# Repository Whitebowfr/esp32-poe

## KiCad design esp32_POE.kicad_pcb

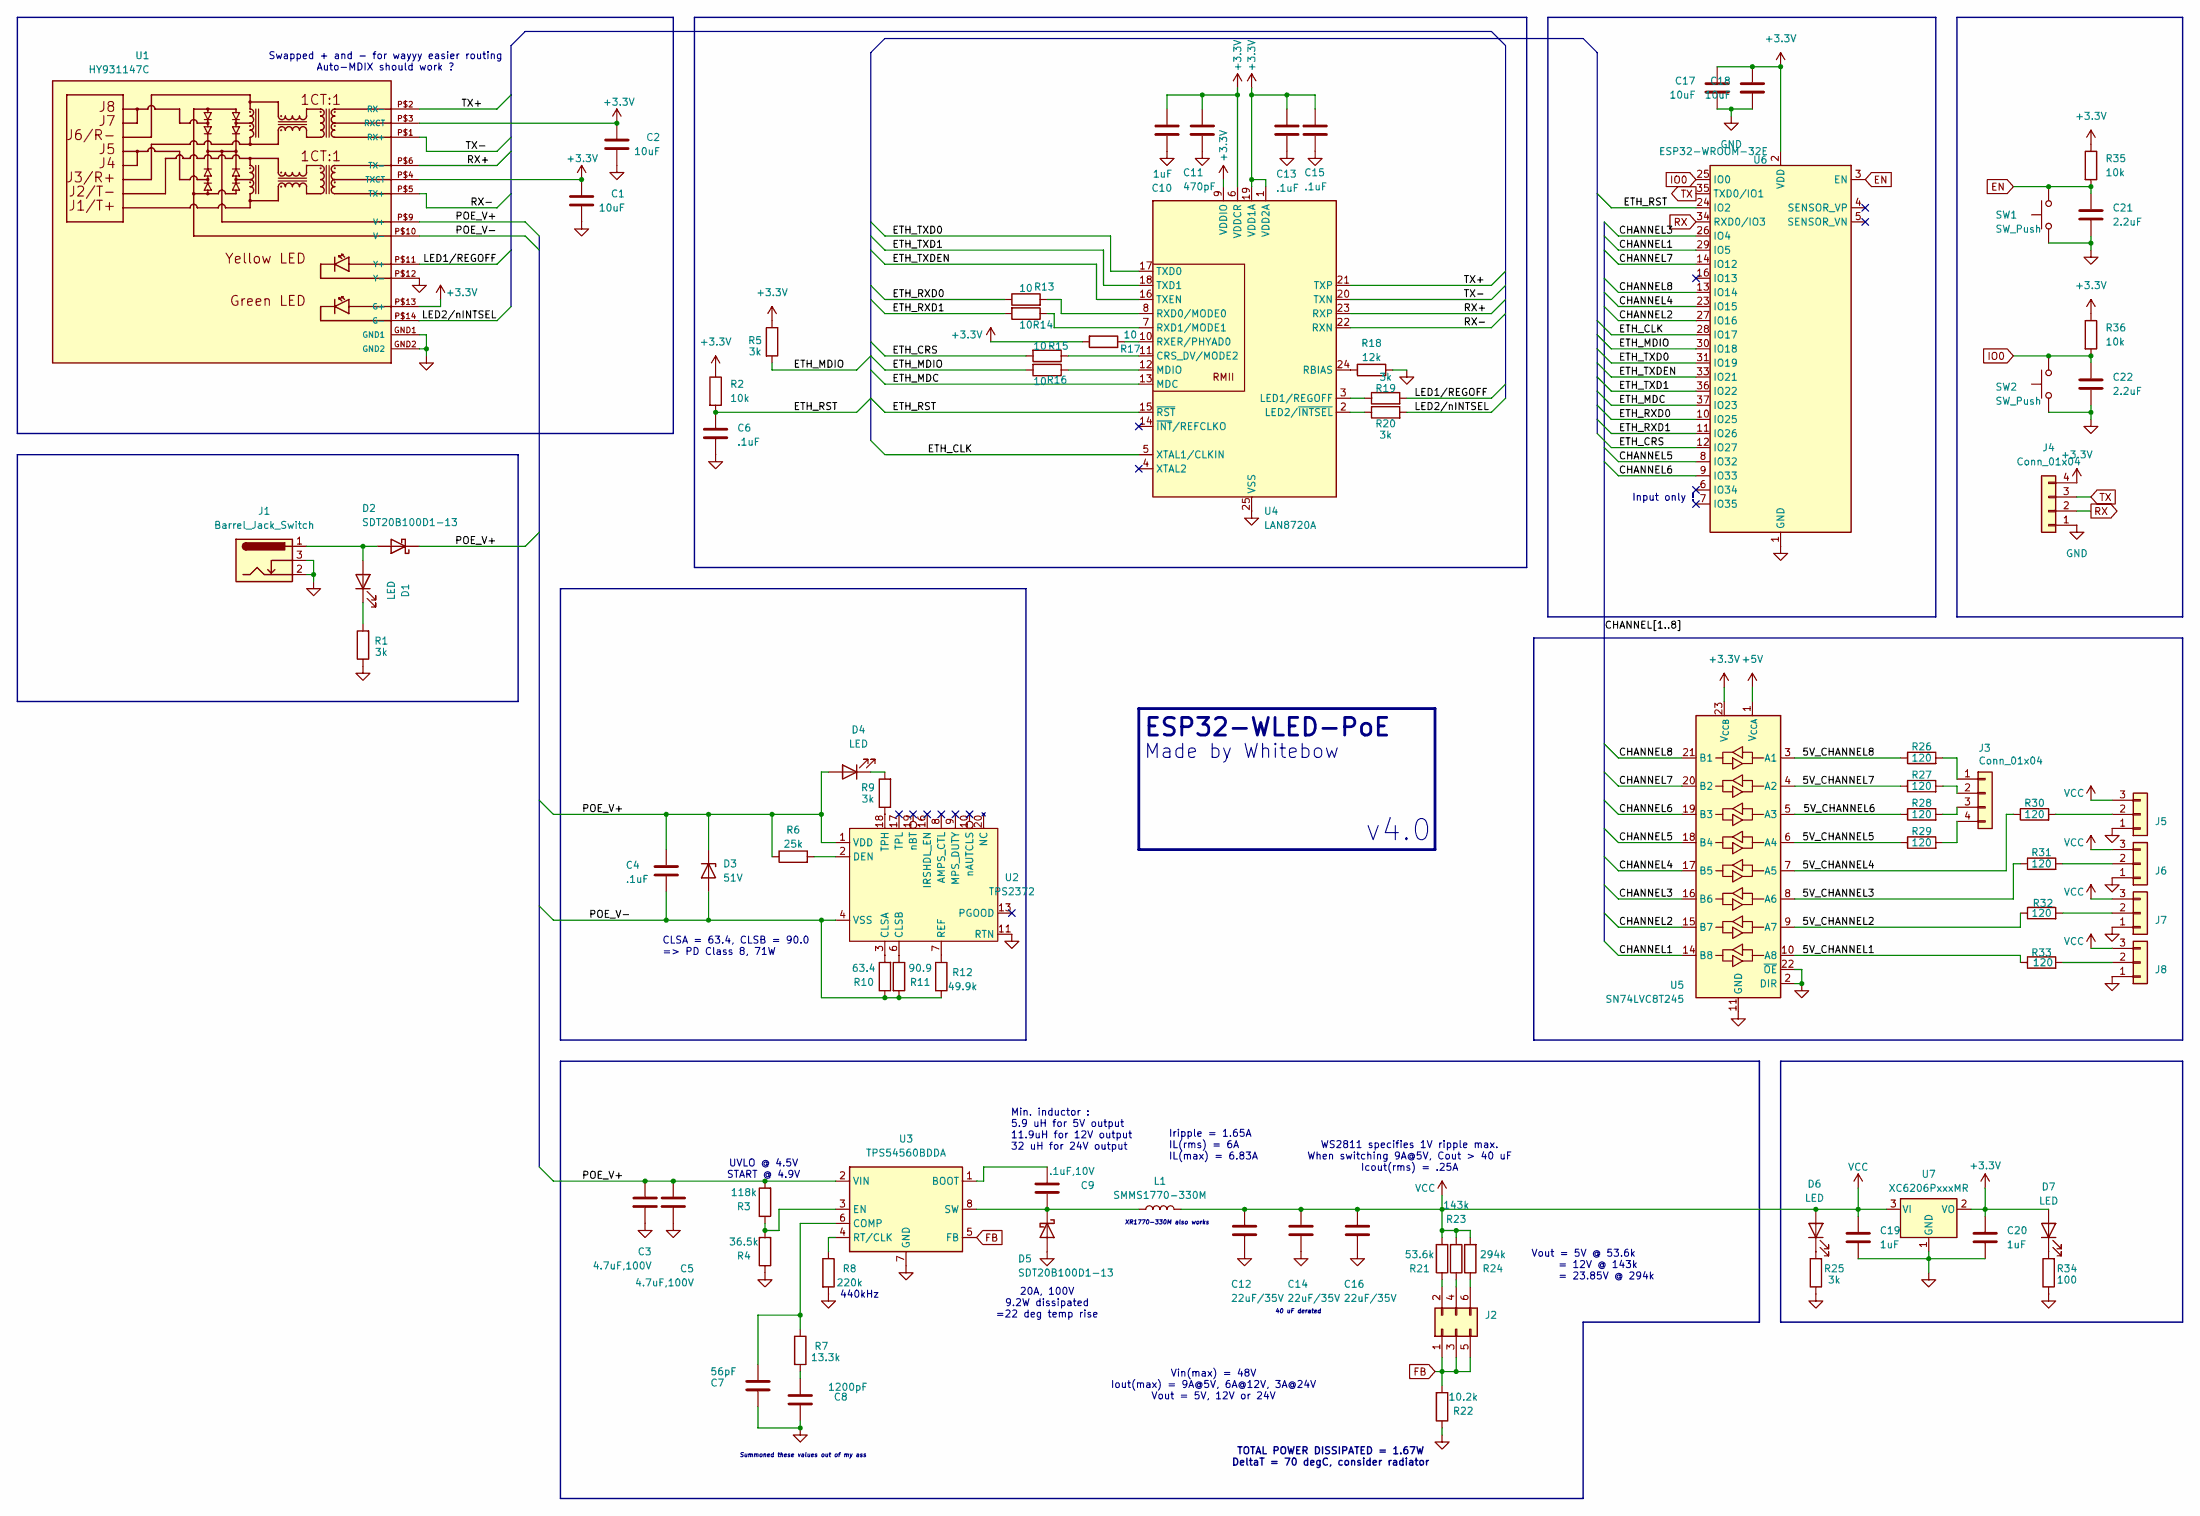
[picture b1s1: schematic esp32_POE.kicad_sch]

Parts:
C1, C2, C17, C18: 10uF; C_0603_1608Metric
C3, C5: 4.7uF,100V; C_1206_3216Metric
C4, C6, C13, C15: .1uF; C_0603_1608Metric
C7: 56pF; C_0603_1608Metric
C8: 1200pF; C_0603_1608Metric
C9: .1uF,10V; C_0603_1608Metric
C10, C19, C20: 1uF; C_0603_1608Metric
C11: 470pF; C_0603_1608Metric
C12, C14, C16: 22uF/35V; C_0805_2012Metric
C21, C22: 2.2uF; C_0603_1608Metric
D1, D4, D6, D7: LED; LED_0603_1608Metric
D2, D5: SDT20B100D1-13; TO-252-2
D3: 51V; D_SMA
J1: Barrel_Jack_Switch; BarrelJack_Horizontal; LCSC C22459638
J2: Conn_02x03_Odd_Even; PinHeader_2x03_P2.54mm_Vertical
J3: Conn_01x04; PinSocket_1x04_P2.54mm_Vertical
J4: Conn_01x04; PinSocket_1x04_P1.27mm_Vertical
J5, J6, J7, J8: Conn_01x03; JST_XH_B3B-XH-AM_1x03_P2.50mm_Vertical
L1: SMMS1770-330M; L_Vishay_IHLP-6767
R1, R5, R9, R19, R20, R25: 3k; R_0603_1608Metric
R2, R35, R36: 10k; R_0603_1608Metric
R3: 118k; R_0603_1608Metric
R4: 36.5k; R_0603_1608Metric
R6: 25k; R_0603_1608Metric
R7: 13.3k; R_0603_1608Metric
R8: 220k; R_0603_1608Metric
R10: 63.4; R_0603_1608Metric
R11: 90.9; R_0603_1608Metric
R12: 49.9k; R_0603_1608Metric
R13, R14, R15, R16, R17: 10; R_0603_1608Metric
R18: 12k; R_0603_1608Metric
R21: 53.6k; R_0603_1608Metric
R22: 10.2k; R_0603_1608Metric
R23: 143k; R_0603_1608Metric
R24: 294k; R_0603_1608Metric
R26, R27, R28, R29, R30, R31, R32, R33: 120; R_0603_1608Metric
R34: 100; R_0603_1608Metric
SW1, SW2: SW_Push; SW_Push_SPST_NO_Alps_SKRK; LCSC C720477
U1: HY931147C
U2: TPS2372; Texas_RGW0020A_VQFN-20-1EP_5x5mm_P0.65mm_EP3.15x3.15mm
U3: TPS54560BDDA; Texas_R-PDSO-G8_EP2.95x4.9mm_Mask2.4x3.1mm_ThermalVias
U4: LAN8720A; VQFN-24-1EP_4x4mm_P0.5mm_EP2.5x2.5mm_ThermalVias
U5: SN74LVC8T245; TSSOP-24_4.4x7.8mm_P0.65mm
U6: ESP32-WROOM-32E
U7: XC6206PxxxMR; SOT-23-3

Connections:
+3.3V: C1.2, C2.2, C10.2, C11.1, C13.1, C15.1, C17.1, C18.1, C20.1, D7.2 (A), J4.4, R2.1, R5.1, R17.2, R35.1, R36.1, U1.P$3 (RXCT), U1.P$4 (TXCT), U1.P$13 (G+), U4.1 (VDD2A), U4.6 (VDDCR), U4.9 (VDDIO), U4.19 (VDD1A), U5.23 (V_{CCB}), U5.24 (V_{CCB}), U6.2 (VDD), U7.2 (VO)
+5V: U5.1 (V_{CCA})
/5V_CHANNEL1: R33.1, U5.10 (A8)
/5V_CHANNEL2: R32.1, U5.9 (A7)
/5V_CHANNEL3: R31.1, U5.8 (A6)
/5V_CHANNEL4: R30.1, U5.7 (A5)
/5V_CHANNEL5: R29.1, U5.6 (A4)
/5V_CHANNEL6: R28.1, U5.5 (A3)
/5V_CHANNEL7: R27.1, U5.4 (A2)
/5V_CHANNEL8: R26.1, U5.3 (A1)
/CHANNEL1: U5.14 (B8), U6.29 (IO5)
/CHANNEL2: U5.15 (B7), U6.27 (IO16)
/CHANNEL3: U5.16 (B6), U6.26 (IO4)
/CHANNEL4: U5.17 (B5), U6.23 (IO15)
/CHANNEL5: U5.18 (B4), U6.8 (IO32)
/CHANNEL6: U5.19 (B3), U6.9 (IO33)
/CHANNEL7: U5.20 (B2), U6.14 (IO12)
/CHANNEL8: U5.21 (B1), U6.13 (IO14)
/ETH_CLK: U4.5 (XTAL1/CLKIN), U6.28 (IO17)
/ETH_CRS: R15.2, U6.12 (IO27)
/ETH_MDC: U4.13 (MDC), U6.37 (IO23)
/ETH_MDIO: R5.2, R16.2, U6.30 (IO18)
/ETH_RST: C6.1, R2.2, U4.15 (~RST), U6.24 (IO2)
/ETH_RXD0: R13.1, U6.10 (IO25)
/ETH_RXD1: R14.2, U6.11 (IO26)
/ETH_TXD0: U4.17 (TXD0), U6.31 (IO19)
/ETH_TXD1: U4.18 (TXD1), U6.36 (IO22)
/ETH_TXDEN: U4.16 (TXEN), U6.33 (IO21)
/LED1/REGOFF: R19.2, U1.P$11 (Y+)
/LED2/nINTSEL: R20.2, U1.P$14 (G-)
/POE_V+: C3.1, C4.1, C5.1, D2.2 (K), D3.1 (K), D4.2 (A), R3.2, R6.1, U1.P$9 (V+), U2.1 (VDD), U3.2 (VIN)
/POE_V-: C4.2, D3.2 (A), R10.1, R11.2, R12.2, U1.P$10 (V-), U2.4 (VSS), U2.5 (VSS), U2.21 (EPAD)
/RX+: U1.P$6 (TX-), U4.23 (RXP)
/RX-: U1.P$5 (TX+), U4.22 (RXN)
/TX+: U1.P$2 (RX-), U4.21 (TXP)
/TX-: U1.P$1 (RX+), U4.20 (TXN)
EN: C21.1, R35.2, SW1.2, U6.3 (EN)
FB: J2.1, J2.3, J2.5, R22.2, U3.5 (FB)
GND: C1.1, C2.1, C3.2, C5.2, C6.2, C7.1, C8.1, C10.1, C11.2, C12.2, C13.2, C14.2, C15.2, C16.2, C17.2, C18.2, C19.2, C20.2, C21.2, C22.2, D5.1 (A), D5.3 (A), J1.2, J1.3, J4.1, J5.1, J6.1, J7.1, J8.1, R1.1, R4.1, R8.2, R18.1, R22.1, R25.1, R34.1, SW1.1, SW2.1, U1.GND1, U1.GND2, U1.P$12 (Y-), U2.11 (RTN), U2.12 (RTN), U3.7 (GND), U3.9 (GND), U4.25 (VSS), U5.2 (DIR), U5.11 (GND), U5.12 (GND), U5.13 (GND), U5.22 (~OE), U6.1 (GND), U6.15 (GND), U6.38 (GND), U6.39 (GND), U7.1 (GND)
IO0: C22.1, R36.2, SW2.2, U6.25 (IO0)
unnamed: C8.2, R7.2
unnamed: D1.2 (A), D2.1 (A), D2.3 (A), J1.1
unnamed: D1.1 (K), R1.2
unnamed: D4.1 (K), R9.2
unnamed: C9.1, D5.2 (K), L1.1, U3.8 (SW)
unnamed: D6.1 (K), R25.2
unnamed: D7.1 (K), R34.2
unnamed: J2.2, R21.1
unnamed: J2.4, R23.1
unnamed: J2.6, R24.1
unnamed: J3.1, R26.2
unnamed: J3.2, R27.2
unnamed: J3.3, R28.2
unnamed: J3.4, R29.2
unnamed: J5.2, R30.2
unnamed: J6.2, R31.2
unnamed: J7.2, R32.2
unnamed: J8.2, R33.2
unnamed: R10.2, U2.3 (CLSA)
unnamed: R11.1, U2.6 (CLSB)
unnamed: R6.2, U2.2 (DEN)
unnamed: R12.1, U2.7 (REF)
unnamed: R9.1, U2.18 (TPH)
unnamed: C9.2, U3.1 (BOOT)
unnamed: C7.2, R7.1, U3.6 (COMP)
unnamed: R3.1, R4.2, U3.3 (EN)
unnamed: R8.1, U3.4 (RT/CLK)
unnamed: R15.1, U4.11 (CRS_DV/MODE2)
unnamed: R19.1, U4.3 (LED1/REGOFF)
unnamed: R20.1, U4.2 (LED2/~INTSEL)
unnamed: R16.1, U4.12 (MDIO)
unnamed: R18.2, U4.24 (RBIAS)
unnamed: R13.2, U4.8 (RXD0/MODE0)
unnamed: R14.1, U4.7 (RXD1/MODE1)
unnamed: R17.1, U4.10 (RXER/PHYAD0)
RX: J4.2, U6.34 (RXD0/IO3)
TX: J4.3, U6.35 (TXD0/IO1)
VCC: C12.1, C14.1, C16.1, C19.1, D6.2 (A), J5.3, J6.3, J7.3, J8.3, L1.2, R21.2, R23.2, R24.2, U7.3 (VI)

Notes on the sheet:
ESP32-WLED-PoE
Vout = 5V @ 53.6k = 12V @ 143k = 23.85V @ 294k
CLSA = 63.4, CLSB = 90.0 => PD Class 8, 71W
TOTAL POWER DISSIPATED = 1.67W DeltaT = 70 degC, consider radiator
Iripple = 1.65A IL(rms) = 6A IL(max) = 6.83A
XR1770-330M also works
Input only !
440kHz
Made by Whitebow
Swapped + and - for wayyy easier routing Auto-MDIX should work ?
40 uF derated
Vin(max) = 48V Iout(max) = 9A@5V, 6A@12V, 3A@24V Vout = 5V, 12V or 24V
UVLO @ 4.5V START @ 4.9V
Min. inductor : 5.9 uH for 5V output 11.9uH for 12V output 32 uH for 24V output
Summoned these values out of my ass
WS2811 specifies 1V ripple max. When switching 9A@5V, Cout > 40 uF Icout(rms) = .25A
20A, 100V 9.2W dissipated =22 deg temp rise
v4.0

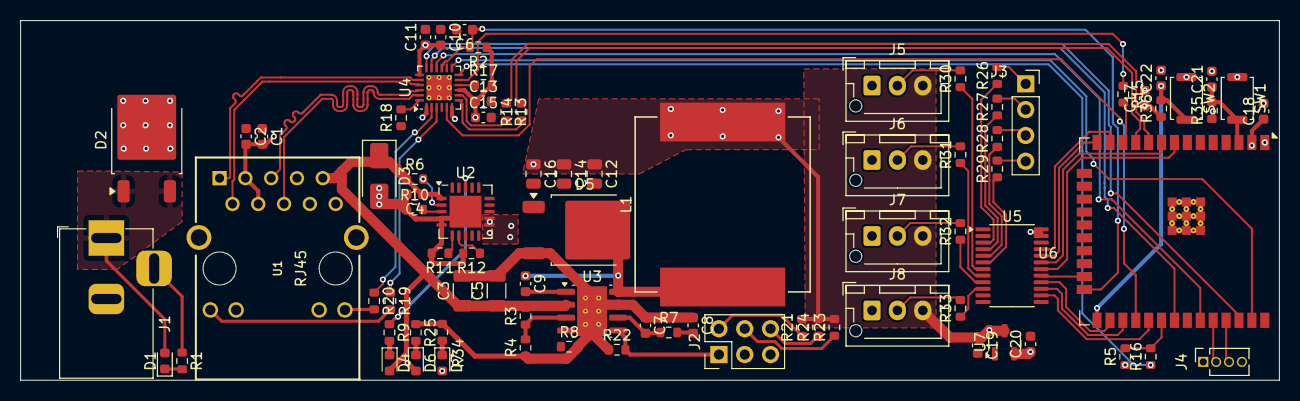
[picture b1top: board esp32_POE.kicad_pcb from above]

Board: 4 copper layers, 123.9 x 35.4 mm, 83 parts (0 on the bottom side), 77 nets.

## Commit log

2025-11-28 Init
2025-11-30 Modified schematic : fixed esp32 circuit, changed to SN74 level shifter, changed to LAN8270
2025-12-01 Finished setting up the schematic, started basic routing
2025-12-03 Finished up roughing pass, reduced pcb size
2025-12-06 Finished 1st routing pass, reduced size of PCB
2025-12-06 Created .gitignore
2025-12-06 Dropped files in gitignore
